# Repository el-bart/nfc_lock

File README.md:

# NFC lock

NFC-based, battery-powered lock for drawers, closets, etc.
android app used to control the module.

## done

* android app communicating with NFC both ways.

## TODO

* PCB with M24SR + STM8S003xx.
* SW for I2C communication with NFC tag.
* SW for controlling 2 servo mechanisms.
* 3D-printed box for servo and battery mounting.

## ideas / improvements

* configurable servos' min/max positions.
* android app look-and-feel update... ;)
* use ATECC508A crypto chip for limiting access to drawer/lock.

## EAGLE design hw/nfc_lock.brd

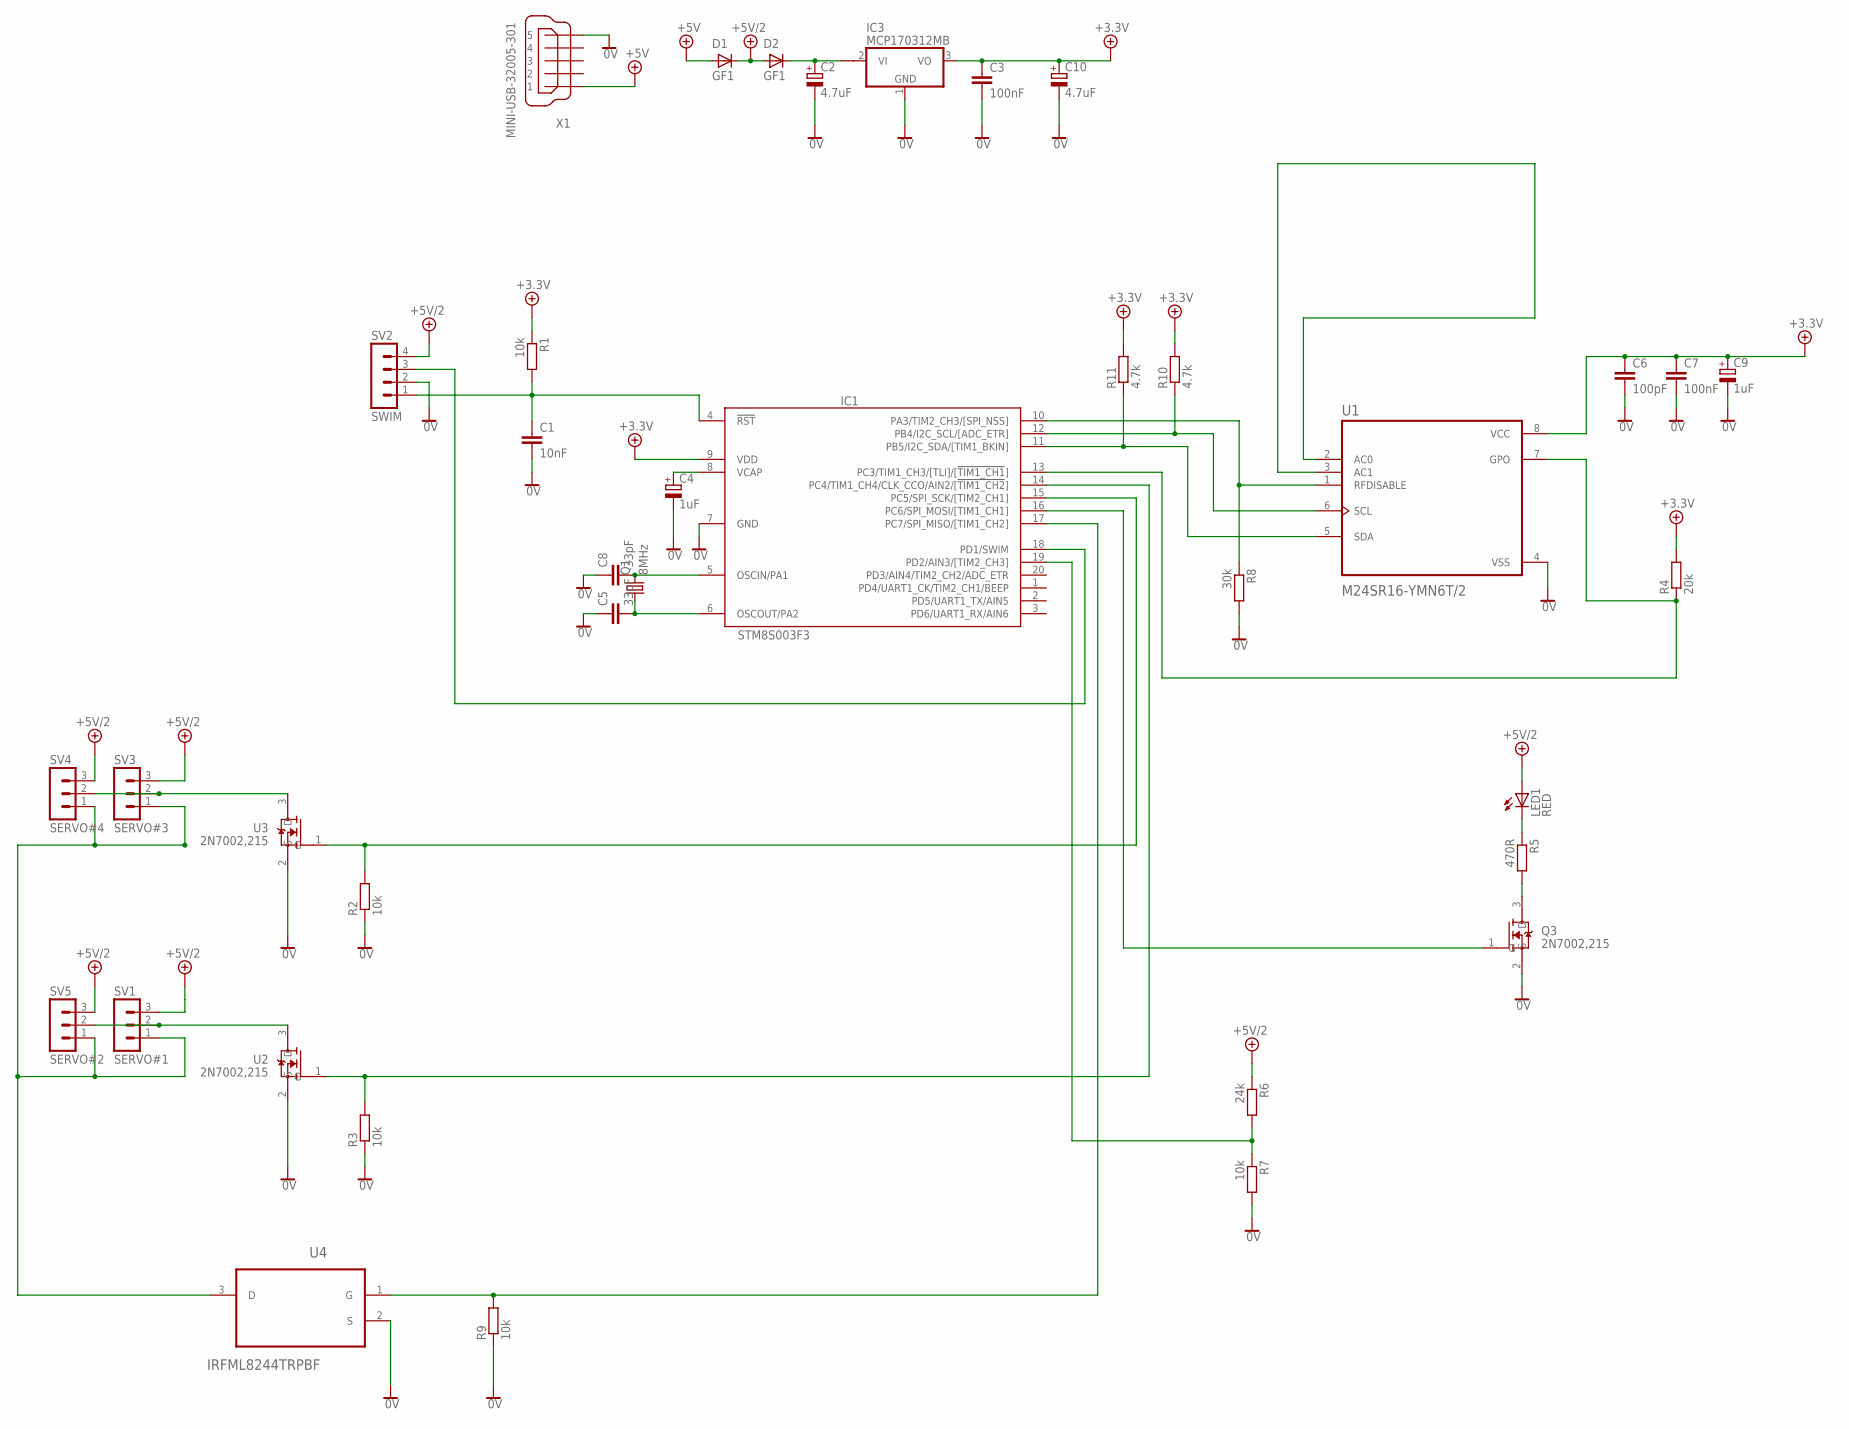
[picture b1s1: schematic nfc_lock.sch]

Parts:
C1: 10nF; C0603K
C2, C10: 4.7uF; 153CLV-0405
C3, C7: 100nF; C1206
C4, C9: 1uF; 153CLV-0405
C5, C8: 33pF; C0603K
C6: 100pF; C1206
D1, D2: GF1; SMA-DO214AC
IC1: STM8S003F3; TSSOP20
IC3: MCP170312MB; SOT89
LED1: RED; CHIP-LED0603
Q1: 8MHz; SM49
Q3: 2N7002,215; SOT95P230X110-3N
R1, R2, R3, R7, R9: 10k; R0805
R4: 20k; R0805
R5: 470R; R0805
R6: 24k; R0805
R8: 30k; R0805
R10, R11: 4.7k; R0805
SV1: SERVO#1; MA03-1
SV2: SWIM; MA04-1
SV3: SERVO#3; MA03-1
SV4: SERVO#4; MA03-1
SV5: SERVO#2; MA03-1
U1: M24SR16-YMN6T/2; SOIC127P600X175-8N
U2, U3: 2N7002,215; SOT95P230X110-3N
U4: IRFML8244TRPBF; SOT95P240X112-3N
X1: MINI-USB-32005-301; 32005-301

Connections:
0V: C1.2, C2.-, C3.2, C4.-, C5.1, C6.2, C7.2, C8.1, C9.-, C10.-, IC1.7 (GND), IC3.1 (GND), Q3.2 (S), R2.1, R3.1, R7.2, R8.2, R9.1, SV2.2, U1.4 (VSS), U2.2 (S), U3.2 (S), U4.2 (S), X1.5
+5V: D1.A, X1.1
+5V/1: C3.1, C6.1, C7.1, C9.+, C10.+, IC1.9 (VDD), IC3.3 (VO), R1.1, R4.2, R10.2, R11.2, U1.8 (VCC)
+5V/2: D1.K (C), D2.A, LED1.A, R6.1, SV1.3, SV2.4, SV3.3, SV4.3, SV5.3
ANTENA: U1.2 (AC0), U1.3 (AC1)
CTRL_LED: IC1.16 (PC6/SPI_MOSI/[TIM1_CH1]), Q3.1 (G)
unnamed: C2.+, D2.K (C), IC3.2@1 (VI1)
unnamed: C1.1, IC1.4 (!RST), R1.2, SV2.1
unnamed: IC1.18 (PD1/SWIM), SV2.3
unnamed: IC1.10 (PA3/TIM2_CH3/[SPI_NSS]), R8.1, U1.1 (RFDISABLE)
unnamed: IC1.13 (PC3/TIM1_CH3/[TLI]/[!TIM1_CH1!]), R4.1, U1.7 (GPO)
unnamed: SV1.2, SV5.2, U2.3 (D)
unnamed: SV3.2, SV4.2, U3.3 (D)
unnamed: LED1.C, R5.1
unnamed: Q3.3 (D), R5.2
unnamed: C4.+, IC1.8 (VCAP)
unnamed: C8.2, IC1.5 (OSCIN/PA1), Q1.2
unnamed: C5.2, IC1.6 (OSCOUT/PA2), Q1.1
unnamed: IC1.19 (PD2/AIN3/[TIM2_CH3]), R6.2, R7.1
SCL: IC1.12 (PB4/I2C_SCL/[ADC_ETR]), R10.1, U1.6 (SCL)
SDA: IC1.11 (PB5/I2C_SDA/[TIM1_BKIN]), R11.1, U1.5 (SDA)
SERVO_GND: SV1.1, SV3.1, SV4.1, SV5.1, U4.3 (D)
SERVO_PACK_1: IC1.14 (PC4/TIM1_CH4/CLK_CCO/AIN2/[!TIM1_CH2!]), R3.2, U2.1 (G)
SERVO_PACK_2: IC1.15 (PC5/SPI_SCK/[TIM2_CH1]), R2.2, U3.1 (G)
SERWO_PWR: IC1.17 (PC7/SPI_MISO/[TIM1_CH2]), R9.2, U4.1 (G)

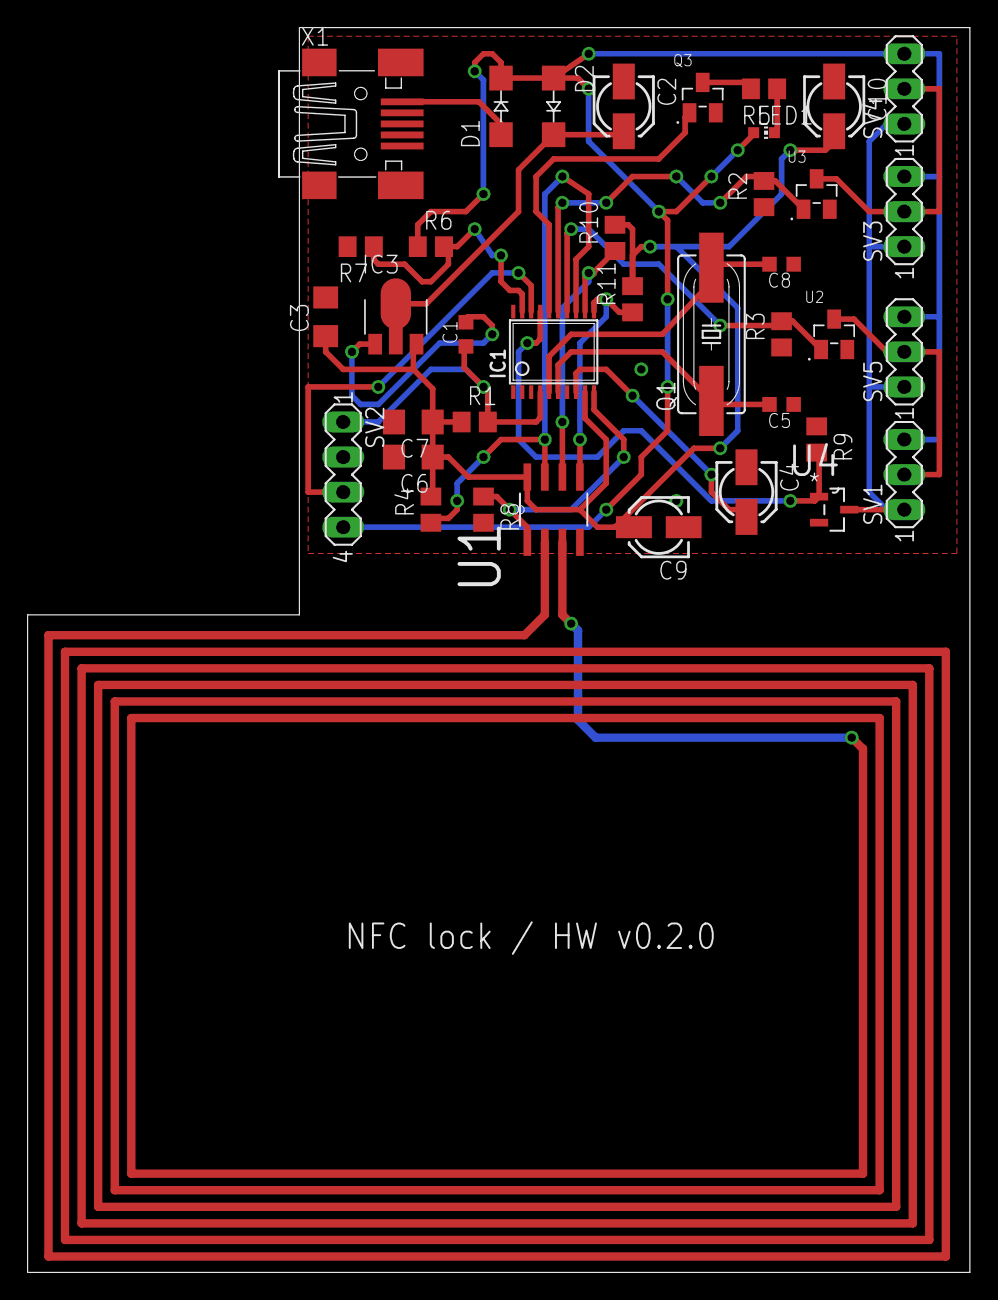
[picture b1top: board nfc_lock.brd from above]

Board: 2 copper layers, 68.2 x 90.2 mm, 38 parts (0 on the bottom side), 25 nets.

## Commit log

2017-12-09 datasheets of ICs to be used
2017-12-09 library for STM8S003x3
2017-12-09 initial - First android NFC app :)
2017-12-09 short project description
2017-12-09 progress list + ideas
2017-12-13 STM8S/STM8A reference manual
2017-12-14 guide for antena design for NFC modules
2017-12-14 empty HW project
2017-12-14 ignoring temproary Eagle files
2017-12-14 M24SR16-YMN6T/2 eagle library
2017-12-14 CPU + NFC
2017-12-14 3.3 voltage regulators + I2C lines
2017-12-14 3.3V/250mA voltage regulator
2017-12-14 power supply circut
2017-12-14 TODO for non-soldering power supply
2017-12-14 power supply pads added
2017-12-14 USB powersupply
2017-12-14 added capacitors values
2017-12-14 STM8/SWIM pin diagram
2017-12-14 power n-mosfet
2017-12-14 irfml8244pbf power n-mosfet eagle library
2017-12-14 added more lines and power n-mosfet to schema
2017-12-14 added new list of TODOs, not to get lost
2017-12-14 TODO for LED
2017-12-14 2x n-mosfet for PWM of servos
2017-12-14 mini-USB is now a power-supply :)
2017-12-19 added SWIM, connections to servos, signalling LED
2017-12-19 resistors not LEDs for voltage split
2017-12-28 TODO: txt -> markdown
2017-12-28 typo + TODO on dual-channel serwo control
2018-01-07 antenna layout datasheet
2018-01-07 antenna drawed
2018-01-07 added 2x more servos + some elements positioning
2018-01-07 all airewires routed - input for some optimizations
2018-01-07 PCB shrinked + board name and revision added
2018-01-07 antenna's surronding space limited
2018-01-07 fixed/approved all found warnings and errors
2018-01-07 fixed packaging of 2n7002 transistor
2018-01-07 all docs are now lower case
2018-01-07 added datasheet for transistor for LED driving
2018-01-07 USB moved to the very edge of the board
2018-01-07 bard dimentions decreased even further
2018-01-07 adjusted sizes of different components to match what i have in a closet... ;)
2018-01-09 added on/off transistor for servos. replaced transistor for PWM servo control. added names to the most important signal lines.
2018-01-20 schematic files for test antenas for M24SR
2018-01-20 TODO updated
2018-01-21 TODOs from https://www.elektroda.pl/rtvforum/viewtopic.php?p=16978634
2018-01-21 schmatics and PCB layout for m24sr-discovery board
2018-01-22 more TODOs on issues with PCB
2018-01-22 reference gerber files for different antena designs from ST
2018-01-26 gerber files moved to a different dir
2018-01-26 top layer converted with a REA tool
2018-01-26 bottom part of the antena layouts
2018-01-31 added pull-ups for I2C and m24sr Vcc decoupling; changed antena type to single-sided
2018-01-31 lcearence and spacing fixed
2018-02-04 additional 4.7uF for general power decoupling
2018-02-04 quartz's capacitors changed from 0402 to 0603K
2018-03-07 STM8S StdPeriph code from ST + a note
2018-03-07 applied Georg Icking-Konert's patch for SPL v2.2.0
2018-03-07 dos2unix for haven's sake...
2018-03-26 ignoring VIM files
2018-03-26 ignoring content of build dir
2018-03-26 CMake-based build - WIP
2018-03-26 interruption things
2018-03-26 all ST's code moved to 'st' dir
2018-03-26 added more source for evaluation board
2018-03-26 test app build in progress...
2018-03-26 updated build settings
2018-03-26 fixed flags to setup compiler for STM8, not 8051
2018-03-28 ignoring ctags
2018-03-28 replaced example_beep that was designed for evaluation board (not discovery board), with example_gpio, that is slightly modified to work with discovery board
2018-03-28 moved ST's StdPeriph to a dir up, to keep it simple
2018-03-28 small cleanup of apps + added target to flash created binaries
2018-03-28 update CMakeLists.txt to new dir structure (ST's part)
2018-03-28 1st PoC for blinking leds (found somewhere on the net)
2018-03-28 PoC removed, as this is already covered by other example
2018-03-28 added proper µC type for final target
2018-03-28 platform is now selectable via parameter
2018-03-28 TODO added for default values
2018-04-17 #ifdef for LED pins, on a per-board basis
2018-04-17 dos2unix on example project files
2018-04-17 example's readme replaced with sth more useful
2018-04-17 removed crappy comments and simplified the syntax a bit
